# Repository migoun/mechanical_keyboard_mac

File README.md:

# Mechanical Keyboard on Mac with simple backlight<br>
This is an example for building a custom mechanical keyboard from scratch. I use it on a Mac, but there is no hardwired difference to a PC keyboard. I even kept the keymapping, because Mac OS can switch the Command and Option keys natively.<br>
Besides the technical side, I'll also write about my experience with manufacturers and stores, where I got all the parts. I also made a few beginner mistakes, which other beginners can avoid by reading this. This whole story is written for beginners.
<br><br>

I've built 2 keyboards with the same layouts but different components. <br><br>
1.) Cherry MX Brown Switches, Custom printed keycaps, green LEDs, black / transparent acrylic case<br>
<br>
<br>
<br>
2.) Gateron black switches, chrome- and bronze sprayed keycaps, fully transparent acrylic case and amber LEDs<br>
<br>
<br>
<br>

<div id="toc_container">
<p class="toc_title">Contents</p>
<ul class="toc_list">
    <li><a href="#crashcourse">Crash Course</a></li>    
    <li><a href="#layoutcreation">Layout Creation</a></li>
    <li><a href="#schematic">Schematic</a></li>
    <li><a href="#pcbdesign">PCB Design</a></li>
    <li><a href="#pcbproduction">PCB Production</a></li>
    <li><a href="#components">Components</a></li>
    <li><a href="#switches">Switches and Stabilizers</a></li>
    <li><a href="#keycaps">Keycaps</a></li>
    <li><a href="#lasering">Lasering a Sandwich Case</a></li>
    <li><a href="#soldering">Soldering and assembling</a></li>
    <li><a href="#firmware">Firmware</a></li>
    <li><a href="#mistakes">Mistakes</a></li>
</ul>
</div>

<h3 id="crashcourse">Crash Course</h3>
There's a phenomenal guide on how to build a keyboard here: https://github.com/ruiqimao/keyboard-pcb-guide <br>
If you don't have a clue yet, and have to start from the very beginning, then that's your starting point. I did it as well, because I had no idea from anything when I started. Through this guide I learned what components are needed to build a mechanical keyboard, what techniques / software is used to design electronic circuit boards, and a lot about electronics in general. Without this guide, I'd have never started.<br><br>

<h3 id="layoutcreation">Layout Creation</h3>
First, get an idea of how your keyboard should look like: http://www.keyboard-layout-editor.com<br>
This is mine: <a href="http://www.keyboard-layout-editor.com/#/gists/c6ae22aae21851b44d510154a7a343f7">Migouner</a>
<br>

<br>
<h3 id="schematic">Schematic</h3>
I did mostly everything like in the keyboard-pcb-guide tutorial. But I needed a different microcontroller, because I wanted to build a bigger keyboard with 85 keys. So with all rows and columns, I needed a total of 27 input pins for the matrix. Because QMK's firmware is used to flash the MCU, I took the one supported by QMK - AT90USB1286. It has a total of 48 input pins, so more than enough for Matrix and LED control pin.<br><br>
This is an overview of the board. Separated in 3 parts. LED circuit, keyboard matrix and the MCU section.<br><br>
<br><br>

MCU and Matrix circuit:<br>
<br>
<br>
<br>
For the matrix, I just looked at kbfirmware.com, the QMK firmware generator. I connected the keys in the schematic above exactly like the firmware tool defined my cols and rows:<br>
<br><br>

Aditionally the LED's for the backlighting:<br>
<br>
<br>

<h3 id="pcbdesign">PCB design</h3>
Normally you'd have to draw the PCB all by yourself, for all keys you have! I however, used a python script from here: https://github.com/ahtn/keyboard_case_and_pcb_gen<br>
You need the json output from KLE for this script to work. With this it generates a finished layout for all keys on the board. Then you have to put in everything else, MCU, diodes, resistors etc...<br><br>

But there are a few steps to get it working (on a mac). You need Homebrew and a lot of libraries, only then you can execute the script without getting an error:<br>
> brew install pip3 python3<br>
> pip3 install nose tornado solidpython numpy scipy kle pyparsing pyaml<br>
> git clone https://github.com/ahtn/keyboard_case_and_pcb_gen .<br>
<br>
Download json from KLE and then execute:<br>
> plate.py keyboard-layout.json<br>
<br><br>
By the time I needed to troubleshoot this script, I could have drawn the PCB already (now). But when I started, I didn't have any experience with KiCAD, and had no idea of positioning the keys, defining footprints etc...so I thought it would be easier to run a script.<br><br>

I'd also recommend, looking at the keyboard_example.py script in the python folder here. Because after importing your netlist into PCBnew, all existing pieces are on top of each other. So you have to click and drag each one to it's physical place on the board. Especially for the diodes, that can be frustrating, because you have to do this for every switch. That's what I wrote the python script for.<br><br>
After all, this is my result:<br>
<br><br>
You can use the silkscreen to print your own logo or text on the board. Kicad layers: F. Silk = Front Side, B. Silk = Back Side<br>
<br><br>

<h3 id="pcbproduction">PCB Production</h3>
After comparing a few manufacturers, I let it made at easyeda.com. You get an online quote immediately after uploading your Gerber files, and it was a very good price. But I ran into a massive delay because the german customs office. More in the mistakes section below. But the quality was perfectly fine. As I'm writing this, I already made 3 orders there, all of them were really well done and also cheap, compaired to other manufacturers.<br><br>

<h3>LED's for backlight</h3>
This is not as easy as it might sound like. An LED has about 2,1 - 2,3 Volts. Powering a single one with an Output pin of an Atmel Microchip is not a problem. Powering multiple LEDs needs a transistor for taking over the extra power. I took a MOSFET for that. (Before I started this project, I had no idea what a MOSFET is, or how an LED Circuit is powered. If you want to learn this, https://www.tinkercad.com/circuits is a great source for getting in touch with electronics (virtually).<br><br>

That turned out helpful, but I wanted to be 100% sure about this. The last thing I wanted, was that my keyboard burned to dust. So I got a cheap Arduino Uno (16&euro; with a lot of extras), also 2 extra MOSFETs from Amazon, and built up this scenario: <br>
<br>
There were only 330 Ohm resistors in the package, resulting in 5.5 mA going through each LED. I wanted about 8 or 9 mA for appropriate brightness (USB 2.0 can handle up to 500 mA in total). so I calculated here what I needed: http://tinyurl.com/y8kq7h9s<br>
<br>
Source: http://www.falstad.com/circuit/ (Also a great electronics simulator)<br>
<br>
200 Ohm resistors seemed fine for me. To wrap this up: The MOSFET is there because it takes power directly from the source and can handle a big amount of current. The gate controls the amount of current going through the transistor, controling the brightness of the LEDs. Therefore gate is connected to a PWM (Pulse Width Modulation) pin on the MCU. The special thing about this particular transistor is, it doesn't need current at the gate - only Voltage. This protects the Atmel chip and it's PWM pin. This circuit is in parallel mode, so these single color LED's cannot be controlled separately. It should be as easy as possible to build.<br>

<br>
<h3 id="components">Components</h3>
I've ordered everything at Digikey.com. But I recommend would read the shipping faq's carefully. I explain why in the mistakes secion below. Another good choice is mouser.com, it's the same great choice and filtering mechanism.<br>
One shitty thing though, shipping is very expensive (in both stores). So either you pay 20$ for shipping, or order something for more that 60$, in which case shipping is free. At least to Germany. So here's my component list:<br><br>
<table>
<tr><td><b>Quantity</b></td><td><b>Description</b></td></tr>
<tr><td>1</td>		<td>MCU AT90USB1286</td></tr>
<tr><td>10</td>		<td>RES 200 OHM 1% 1/4W 0805</td></tr>
<tr><td>1</td>		<td>CRYSTAL 16.0000MHZ 18PF SMD</td></tr>
<tr><td>1</td>		<td>CAP CER 1UF 16V X7R 0805</td></tr>
<tr><td>100</td>	<td>DIODE GEN PURP 100V 150MA SOD123</td></tr>
<tr><td>10</td>		<td>RES 22 OHM 5% 1/8W 0805</td></tr>
<tr><td>1</td>		<td>CAP CER 4.7UF 25V X5R 0805</td></tr>
<tr><td>1</td>		<td>SWITCH TACTILE SPST-NO 0.05A 12V</td></tr>
<tr><td>1</td>		<td>CONN RCPT MINI USB2.0 5POS SLD</td></tr>
<tr><td>2</td>		<td>CAP CER 22PF 50V C0G/NP0 0805</td></tr>
<tr><td>4</td>		<td>CAP CER 0.1UF 50V X7R 0805</td></tr>
<tr><td>10</td>		<td>RES 10K OHM 5% 1/8W 0805</td></tr>
<tr><td>2</td>		<td>RES SMD 1K OHM 0.1% 1/8W 0805</td></tr>
<tr><td>10</td>		<td>LED GREEN DIFFUSED 1206 SMD</td></tr>
<tr><td>1</td>		<td>MOSFET N-CH 30V 58A DPAK</td></tr>
</table>

<br>
<h3 id="switches">Switches and Stabilizers</h3>
I made the black board with Cherry brown switches, and the transparent one with Gateron black switches. You'll find a lot about switch types yourself, so I won't go into detail here. Interesting was that Gateron costs only half the price of Cherry. It claims to be the same, though. So I wanted to try out both of them. Same goes for stabilizers. Cherry stabs are more expensive than Costar. I used Cherry stabs for the Cherry switches and Costar for the Gateron switches. Good place to find stuff like that is at <a href="https://www.switchtop.com/">Switchtop</a>.<br>
<br>My result: The Cherry Brown Switches were easy to install and fit stable in the mounting holes "MX Openable Cutout". Also typing feels quite good on them. This combination of switches and plate is a robust and solid one. My personal favourite.<br>
The Gaterons are quite good, not a big difference to Cherry. However, the mounting holes I have chosen for the Gaterons when making the mounting plate - "MX + Alps Cutout" - it is known as the least stable. Now I know why. And it saved maybe 1 - 2$ maximum, when lasering the plate. So NOT recommendable. The other MX cutout could be used as well here.<br>
The Costar stabilizers are much more difficult to install, almost not stable at all, and I had to cut them with my wirecutter, so they didn't grind the bracket while going up and down. For me it wasn't fun using them. Clear advantage for the Cherry stabilizers, which fit pretty well and could be installed more quickly.<br>
Also a tube of Superlube is recommendable, greasing the stabilizers makes them go more smoothly.<br><br>
Important: PCB mounting is different from plate mounting. It changes your whole build. Stabilizers and switches are different, the PCB needs another design for drill holes etc, and the mounting plate's switch holes can be different. So be sure which mounting style you want. I went with plate mount, because more stability - the typing pressure is taken by the metal plate instead of the PCB, also fewer drilling holes on the PCB. If your PCB was made for PCB mount, it can also be used for plate mount. Not the other way.<br>

<br>
<h3 id="keycaps">Keycaps</h3>
For the black Rebound Games keyboard, I made custom keycaps at <a href="http://www.maxkeyboard.com/">MaxKeyboard</a>. They got templates for vector software, I use Inkscape. There are some limitations with the colors, but that was fine for my design. So I uploaded my Inkscape file and ordered the key set. Prices for custom printed key sets start at only 20$, so I could live with the color limitations.<br>
What wasn't so nice, some keys were slightly damaged. Looked like burn marks on the edges, but still fully functional. At least the printing was good.
<br><br>
For the second one I've ordered the cheapest keyset I could find on ebay, about 10&euro;. I sprayed them in bronze and chrome colors. In combination with the fully transparent case and the amber LEDs, it should get a futuristic style.<br>

<br>

<br>
<h3 id="lasering">Lasering a sandwich case</h3>
A very handy tool and also your starting point for case design: <a href="http://builder.swillkb.com/">builder.swillkb.com</a><br>
It creates all parts of a sandwich case keyboard, you just have to put in your layout from keyboard-layout-editor.com, and adjust the settings, it's well documented.<br>
<ul>
    <li>Mounting plate<br>
    For most plate mounted MX switches, the plate must be exactly 1.5mm thick. I let it made at <a href="https://www.laserboost.com/">Laserboost</a> in Barcelona and chose natural carbon steel as material. It was the cheapest metal, and I wanted to spray it another color anyway. So I didn't care about finishing. I was super satisfied with the end result!<br>  <br> One plate hat holes for Cherry switches only, the other one for Gateron switches and Costar stabilizers.
    </li><br>
    <li>Acrylic case<br>
    For top-, bottom- and open layers, I found reasonable prices at local companies in Germany. Because I found all the online services for lasercutting acrylic plates way to expensive. The two open layers are 5mm thick each, transparent acryl. Very solid, as it should be. Top- and bottom layers are 1mm each, black acryl. The second keyboard got transparent VIVAK material for top and bottom. It's like acryl but cheaper, I wanted to give it a try. The 1mm plates look fine, but are pretty wobbly. I thought they would be as hard as the thicker plates, but never mind. They don't have to carry something, so it doesn't matter.<br>
    
    </li><br>
    <li>Screws<br>
    My edge padding on the case is 7.4mm. That's the distance from the keys to the border of the case. In the middle of the padding, there are holes for screws. I made 6 in total. Diameter is 3.5mm, needed for M3 screws. It fits perfectly. On the bottom I used nut covers to fixate the screw. It also serves as a nice bottom foot for the keyboard. Finally I glued some rubber feet on the bottom, to get the right typing angle.
    </li><br>
</ul>

<br>
<h3 id="soldering">Soldering and assembling</h3>
If you never soldered SMDs (Surface Mount Devices), I highly recommend a practise pcb before start soldering your board. I bought one for 2&euro; on ebay. Also check out youtube tutorials on how to use Flux, or solder SMD, Microchips etc... You definitely need some magnifier as well, at least for controlling after soldering. I also have a magnifying headset for soldering. Because the chips's pins or the 0805 components are just pretty damn small.<br>
Best is to start with all components EXCEPT for the diodes and switches. A basic setup to make your computer recognize the chip when plugged in. This way you can react to issues at an early stage. And there can be issues! See mistakes section.<br>
If you built the board correctly, you will see a new USB device after plugging it into an USB port on your computer. It's named after the chip in the device manager (Windows), or on Mac "About this Mac" -> "More info".<br>
If you see your device there, you're good to go. If not, grab your multimeter for troubleshooting.<br>
<br>
Especially the diodes only work if the polarity is right. They cannot be the wrong way round. Everything else (besides the MCU and LEDs) can be either way. Capacitors, resistors and even the crystal.<br>
<br>
Once done soldering all components, the stabs and switches can be put in. First the stabs! Then some switches at the corners for fixating the plate on the PCB. If it fits nicely, all the other switches can be assembled and soldered as well. 
<br><br>
<br>
I sprayed the metal plate with a matt black color, it looked amazing afterwards! After the board is soldered and assembled to the mounting plate, all switches and stabs are in, the case can be screwed together and the keycaps put on.<br>

<br>
<h3 id="firmware">Firmware</h3>
I chose <a href="https://docs.qmk.fm">QMK firmware</a>, which is a great open source firmware for mechanical keyboards with lots of interesting features. Including backlight, key macros, debug mode etc...<br>
Your keyboard can be configured easily within the browser <a href="http://kbfirmware.com">kbfirmware.com</a>, things like keymap, pin mapping for the matrix, macros, basically everything. You don't have to write code at this point.<br>
After configuring, you can either download the hex file and flash it to the chip directly, or download the source code via zip file, and build the hex file yourself. That's what I did, because this way I could also customize the USB device Vendor and Version (in config.h), which you see in your device manager. Everything from building to flashing is well documented in the QMK docs. But there is something to take note of, below in the mistakes secion.<br>

<br>
<h3 id="mistakes">Mistakes</h3>
Ok here are some beginners mistakes, some were annoying, some stupid and some not hard to fix. I hope it help avoiding such things.
<ul>
    <li>Ordering with DHL<br>
    DHL scammed me so hard. I chose DHL for shipping, not UPS. So it arrived at the customs office in Leipzig, I got an email saying: Do you want us to ship the package? If you're a reseller, it would cost you extra fees. I said no, I order as a private person, and also paid the order as one. They looked at my 100 diodes position and asked me, why would you order 100 pieces of something? You must be reselling those...So I had to explain them why I would need 100 diodes! At some point they believed me and were willing to ship it. I asked the person on the phone if it would cost me something, taxes, fees etc...? If so, I do NOT want the package to be delivered. They said no, it does NOT cost anything, and shipped it. 4 weeks later I got a letter from DHL in cooperation with customs, forcing me to pay 40 Euros!!! for DHL "services"! What services please? It was free shipping you bunch of criminals! So i bought at Digikey for 50&euro; (FREE SHIPPING), and DHL rips 40&euro; off my face. And you can't do shit about it. If you deny the payment, you get extra fees on top of it.<br>
    Next time I ordered with UPS on a Friday, on Monday I had it. And NO extra fees! So never trust DHL, don't believe a single word they say. And if you order there from another continent, record every phone call and get yourself very good lawyers!<br><br>  
    </li><br>
    <li>PCB<br>
    On my first attempt, I didn't get the computer recognize the device. It just nothing happend after plugging into different USB ports. But power on all the SMD components seemed fine after measuring with my multimeter. In the end, it was wrong PCB design! I didn't connect the VBus pin of the Microcontroller! That was incredible stupid because this pin is responsible for registering an USB device on the computer. Not only that, but on this pin there must be a capacitor, which I also didn't consider. So this was my try to fix it:<br><br>I bridged a capacitor to the pin. Of course it didn't work and i threw away all 5 PCB's!<br><br>At least I could keep the components and reuse them on the next board.<br><br>
    </li>
    <li>Hint<br>
    If you want to save money, it maybe a good idea to start small. This way you won't fail at the end product like I did. I had to order this PCB twice, second time with the VBus corrected. For 2$ you can design a little board like this and try it out, get used to micro chips and how they work. For me it worked right after soldering. <br> <br>I then connected some LEDs and switches from my Arduino and flashed QMK firmware on the chip. To make a 4 key keyboard. It worked perfectly fine.<br><br> At this point I was sure what I'm doing, and ready to spend more money for the next keyboard PCB.<br>
    </li><br>
    <li>Switch Cutouts<br>
    I forgot to rotate vertical keys on the PCB, in the Case &amp; Plate builder the cutouts were rotated automatically. So the return key and the two vertical keys on the numblock were rotated by 90&deg; on the mounting plate, but not on the PCB. The Cherry and Gateron switches both fit the holes anyway, but without fixating. They are kept there by soldering only. Luckily assembling was possible anyway with Cherry. With Costar however, no luck. The keycap wouldn't fit on a 90&deg; rotated switch with opposite Costar stabs. So I had to remove the stabs completely there, resulting in a wobbly key.<br>
    </li><br>
    <li>LEDs<br>
    The LEDs I've ordered were too weak. They almost didn't illuminate at all. Turns out they were "Indication" LEDs. What I needed though, were Illumination LEDs. I didn't know which parameter in the datasheet actually stands for light intensity, and found that "mcd" is the one (Millicandela). The LEDs just had 8 mcd, which is close to nothing. Then I've ordered some other LEDs on ebay for 2&euro;. They had about 550 mcd and were nice and bright! They are on the picture at the top, the green ones.<br>
    Of course they had to be of the same current (20mA) and mounting type 1206.<br>
    </li><br>
    <li>Firmware<br>
    QMK is awesome. I just found 2 issues:<br>
    If you download the zip file directly from the firmware builders website, you cannot compile it. Because the codebase on the website is too old. A workaround is to download the git repository from qmk - it's documented in their docs - take your keyboard's directory from your zip file (not the other files), and put it into the QMK repo you've just cloned with git, also into the keyboards folder. Rename the folder to ["your keyboards name"]. Just like all other folders in there.<br>
    Then you can build the hex file with this command: make ["your keyboards name"]<br>
    Then it still won't work, saying some event function cannot be found. Just delete the whole funtion from your keymap.c file and it should run.<br>
    Also the loop for the backlight breathing was not correct, it flickered and then restarted every time, looked strange. It must be fixed in quantum/quantum.c.<br> 
    </li><br>
</ul><br>
<br>
That's all I have to say about it. It was not cheap but I learned very much about electronics, PCB's, microcontrollers... and got an ass kicking keyboard now, which I use every day and indeed became my favourite one! So I feel like it was worth it :-) I hope it helps you guys who also want to start building a keyboard. Have fun!

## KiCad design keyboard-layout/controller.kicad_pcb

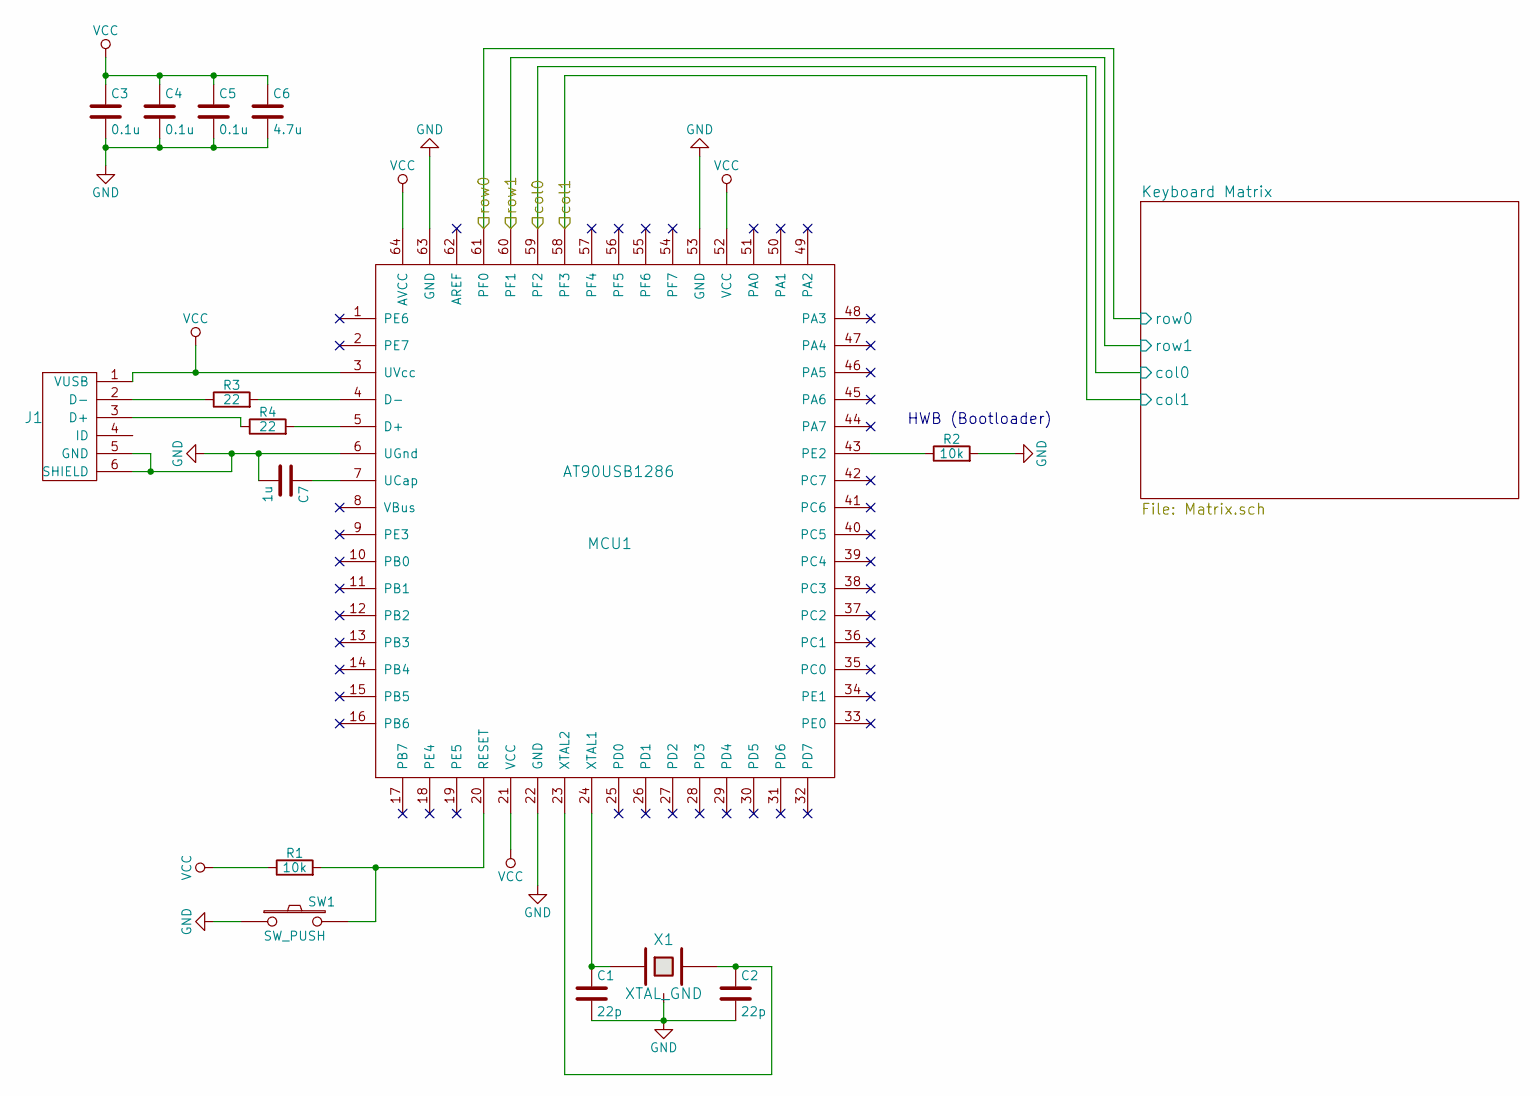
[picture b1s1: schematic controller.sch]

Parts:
C1, C2: 22p; C_0805_HandSoldering
C3, C4, C5: 0.1u; C_0805_HandSoldering
C6: 4.7u; C_0805_HandSoldering
C7: 1u; C_0805_HandSoldering
J1: USB_mini_micro_B; USB_miniB_hirose_5S8
MCU1: AT90USB1286; QFP80P1600X1600X120-64N
R1, R2: 10k; R_0805_HandSoldering
R3, R4: 22; R_0805_HandSoldering
SW1: SW_PUSH; SW_SPST_TL3342
X1: XTAL_GND; Crystal_SMD_SeikoEpson_FA238-4pin_3.2x2.5mm

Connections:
/Keyboard Matrix/col0: MCU1.59 (PF2); also elsewhere on the board
/Keyboard Matrix/col1: MCU1.58 (PF3); also elsewhere on the board
/Keyboard Matrix/row0: MCU1.61 (PF0); also elsewhere on the board
/Keyboard Matrix/row1: MCU1.60 (PF1); also elsewhere on the board
GND: C1.2, C2.2, C3.2, C4.2, C5.2, C6.2, C7.2, J1.5 (GND), J1.6 (SHIELD), MCU1.6 (UGnd), MCU1.22 (GND), MCU1.53 (GND), MCU1.63 (GND), R2.2, SW1.1, X1.3
unnamed: C1.1, MCU1.24 (XTAL1), X1.1
unnamed: C2.1, MCU1.23 (XTAL2), X1.2
unnamed: C7.1, MCU1.7 (UCap)
unnamed: J1.2 (D-), R3.1
unnamed: J1.3 (D+), R4.1
unnamed: MCU1.4 (D-), R3.2
unnamed: MCU1.5 (D+), R4.2
unnamed: MCU1.20 (RESET), R1.2, SW1.2
unnamed: MCU1.43 (PE2), R2.1
VCC: C3.1, C4.1, C5.1, C6.1, J1.1 (VUSB), MCU1.3 (UVcc), MCU1.21 (VCC), MCU1.52 (VCC), MCU1.64 (AVCC), R1.1

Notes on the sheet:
HWB (Bootloader)

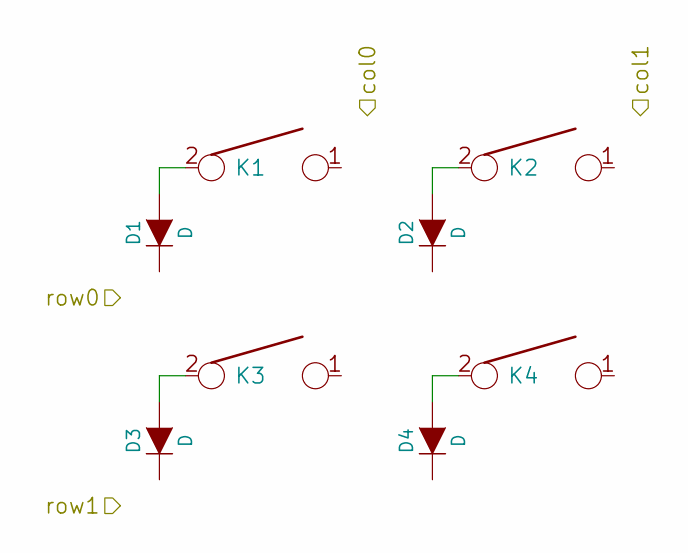
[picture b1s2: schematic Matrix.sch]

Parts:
D1, D2, D3, D4: D; D_SOD123_axial
K1, K2, K3, K4: KEYSW; MX1A

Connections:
/Keyboard Matrix/col0: K1.1, K3.1; also elsewhere on the board
/Keyboard Matrix/col1: K2.1, K4.1; also elsewhere on the board
/Keyboard Matrix/row0: D1.1 (K), D2.1 (K); also elsewhere on the board
/Keyboard Matrix/row1: D3.1 (K), D4.1 (K); also elsewhere on the board
unnamed: D1.2 (A), K1.2
unnamed: D2.2 (A), K2.2
unnamed: D3.2 (A), K3.2
unnamed: D4.2 (A), K4.2

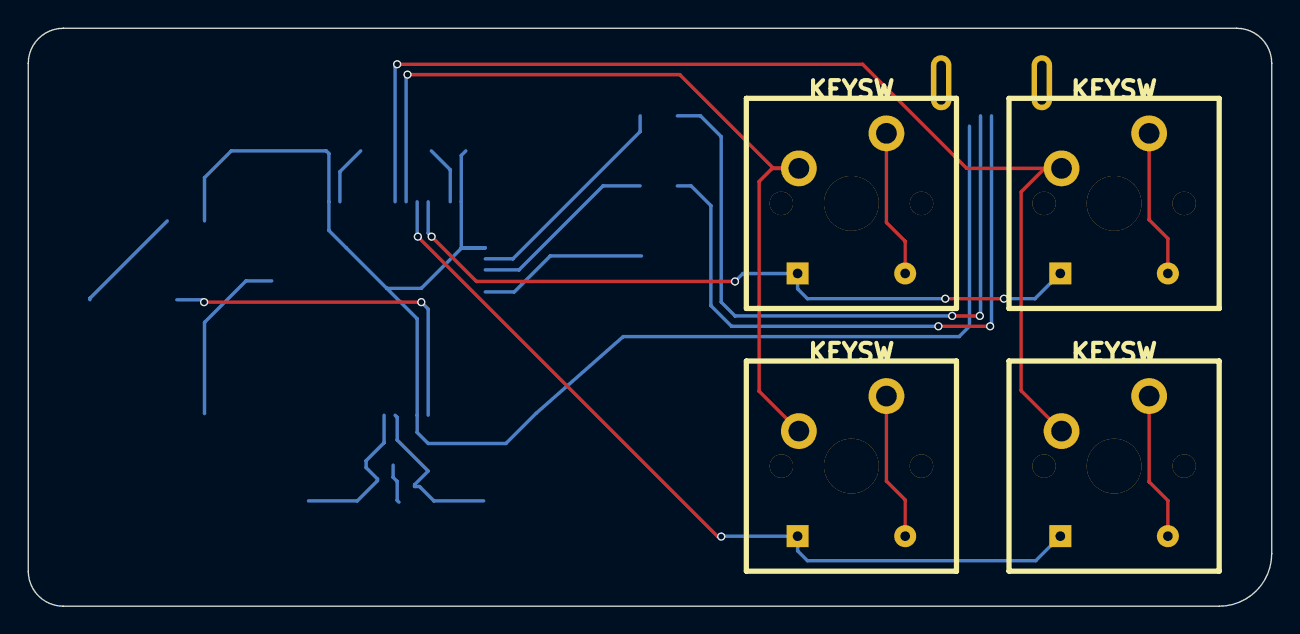
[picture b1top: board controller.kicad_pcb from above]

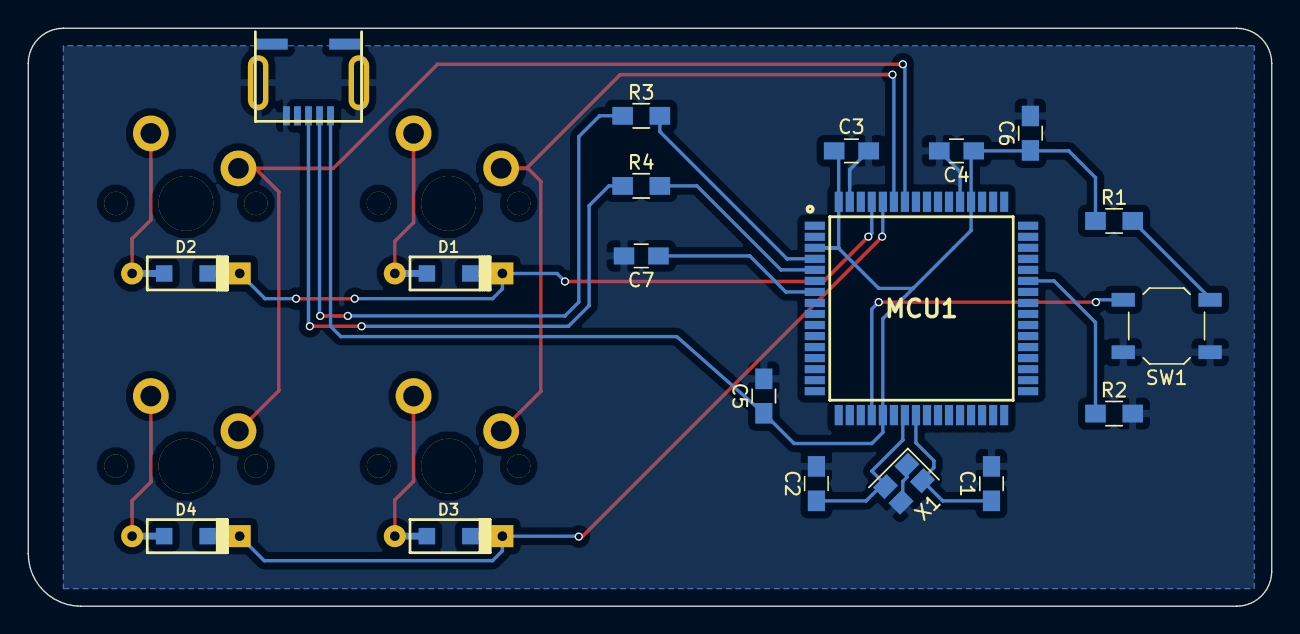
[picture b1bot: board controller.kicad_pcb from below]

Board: 2 copper layers, 90.2 x 41.9 mm, 23 parts (19 on the bottom side), 19 nets.

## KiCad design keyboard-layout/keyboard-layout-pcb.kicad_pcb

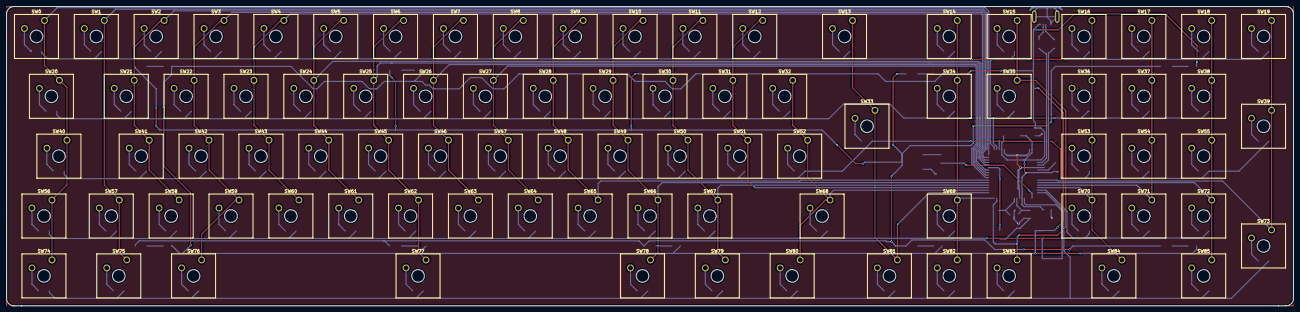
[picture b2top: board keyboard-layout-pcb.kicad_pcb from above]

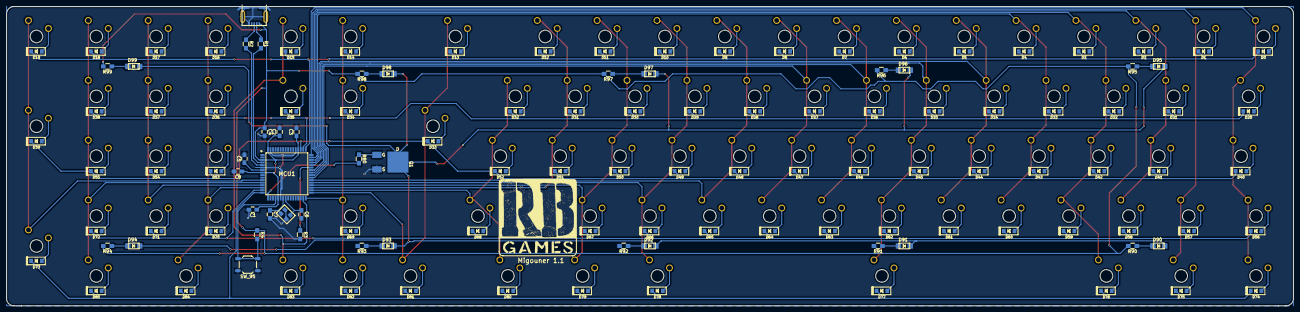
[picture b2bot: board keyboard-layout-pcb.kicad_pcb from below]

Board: 2 copper layers, 408.5 x 95.0 mm, 210 parts (124 on the bottom side), 136 nets.

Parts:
C1, C2, C3, C8: 0.1u; C_0805_HandSoldering
C4: 4.7u; C_0805_HandSoldering
C5: 1u; C_0805_HandSoldering
C6, C7: 22p; C_0805_HandSoldering
D0, D1, D2, D3, D4, D5, D6, D7, D8, D9, D10, D11, D12, D13, D14, D15, D16, D17, D18, D19, D20, D21, D22, D23, D24, D25, D26, D27, D28, D29, D30, D31, D32, D33, D34, D35, D36, D37, D38, D39, D40, D41, D42, D43, D44, D45, D46, D47, D48, D49, D50, D51, D52, D53, D54, D55, D56, D57, D58, D59, D60, D61, D62, D63, D64, D65, D66, D67, D68, D69, D70, D71, D72, D73, D74, D75, D76, D77, D78, D79, D80, D81, D82, D83, D84, D85: D; D_SOD123W_hand
D90, D91, D92, D93, D94, D95, D96, D97, D98, D99: LED; SMD_LED_Green_Migist
J1: USB_mini_micro_B; USB_miniB_hirose_5S8
MCU1: AT90USB1286; QFP80P1600X1600X120-64N
Q1: Mosfet; MOSFET
R1, R2: 22; R_0805_HandSoldering
R3, R4: 10k; R_0805_HandSoldering
R80: 1k; R_0805_HandSoldering
R90, R91, R92, R93, R94, R95, R96, R97, R98, R99: R; R_0805_HandSoldering
SW0, SW1, SW2, SW3, SW4, SW5, SW6, SW7, SW8, SW9, SW10, SW11, SW12, SW14, SW15, SW16, SW17, SW18, SW19, SW21, SW22, SW23, SW24, SW25, SW26, SW27, SW28, SW29, SW30, SW31, SW32, SW34, SW35, SW36, SW37, SW38, SW41, SW42, SW43, SW44, SW45, SW46, SW47, SW48, SW49, SW50, SW51, SW52, SW53, SW54, SW55, SW57, SW58, SW59, SW60, SW61, SW62, SW63, SW64, SW65, SW66, SW67, SW69, SW70, SW71, SW72, SW81, SW82, SW83, SW85: KEYSW; SW_Cherry_MX1A_1.00u_Plate
SW13, SW84: KEYSW; SW_Cherry_MX1A_2.00u_Plate
SW20: KEYSW; SW_Cherry_MX1A_1.50u_Plate
SW33: KEYSW; SW_Cherry_MX1A_ISOEnter_Plate
SW39, SW73: KEYSW; SW_Cherry_MX1A_2.00u_Vertical_Plate
SW40: KEYSW; SW_Cherry_MX1A_1.75u_Plate
SW56, SW74, SW75, SW76, SW78, SW79, SW80: KEYSW; SW_Cherry_MX1A_1.25u_Plate
SW68: KEYSW; SW_Cherry_MX1A_2.75u_Plate
SW77: KEYSW; SW_Cherry_MX1A_6.25u_Plate
SW_95: SW_PUSH; SW_SPST_TL3342
X1: XTAL_GND; FA-238

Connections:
/Keyboard Matrix/col0: MCU1.48, SW0.1, SW20.1, SW40.1, SW56.1, SW74.1
/Keyboard Matrix/col1: MCU1.47, SW1.1, SW57.1, SW75.1
/Keyboard Matrix/col2: MCU1.46, SW2.1, SW21.1, SW41.1, SW58.1
/Keyboard Matrix/col3: MCU1.45, SW3.1, SW22.1, SW42.1, SW59.1, SW76.1
/Keyboard Matrix/col4: MCU1.44, SW4.1, SW23.1, SW43.1, SW60.1
/Keyboard Matrix/col5: MCU1.42, SW5.1, SW24.1, SW44.1, SW61.1
/Keyboard Matrix/col6: MCU1.41, SW6.1, SW25.1, SW45.1, SW62.1, SW77.1
/Keyboard Matrix/col7: MCU1.40, SW7.1, SW26.1, SW46.1, SW63.1
/Keyboard Matrix/col8: MCU1.39, SW8.1, SW27.1, SW47.1, SW64.1
/Keyboard Matrix/col9: MCU1.38, SW9.1, SW28.1, SW48.1, SW65.1
/Keyboard Matrix/col10: MCU1.37, SW10.1, SW29.1, SW49.1, SW66.1, SW78.1
/Keyboard Matrix/col11: MCU1.36, SW11.1, SW30.1, SW50.1, SW67.1, SW79.1
/Keyboard Matrix/col12: MCU1.35, SW12.1, SW31.1, SW51.1
/Keyboard Matrix/col13: MCU1.34, SW32.1, SW52.1, SW68.1, SW80.1
/Keyboard Matrix/col14: MCU1.33, SW13.1, SW33.1, SW81.1
/Keyboard Matrix/col15: MCU1.32, SW14.1, SW34.1, SW69.1, SW82.1
/Keyboard Matrix/col16: MCU1.31, SW15.1, SW35.1, SW83.1
/Keyboard Matrix/col17: MCU1.14, SW16.1, SW36.1, SW53.1, SW70.1, SW84.1
/Keyboard Matrix/col18: MCU1.13, SW17.1, SW37.1, SW54.1, SW71.1
/Keyboard Matrix/col19: MCU1.12, SW18.1, SW38.1, SW55.1, SW72.1, SW85.1
/Keyboard Matrix/col20: MCU1.11, SW19.1, SW39.1, SW73.1
/Keyboard Matrix/row0: D0.1, D1.1, D2.1, D3.1, D4.1, D5.1, D6.1, D7.1, D8.1, D9.1, D10.1, D11.1, D12.1, D13.1, D14.1, D15.1, D16.1, D17.1, D18.1, D19.1, MCU1.49
/Keyboard Matrix/row1: D20.1, D21.1, D22.1, D23.1, D24.1, D25.1, D26.1, D27.1, D28.1, D29.1, D30.1, D31.1, D32.1, D34.1, D35.1, D36.1, D37.1, D38.1, MCU1.50
/Keyboard Matrix/row2: D33.1, D39.1, D40.1, D41.1, D42.1, D43.1, D44.1, D45.1, D46.1, D47.1, D48.1, D49.1, D50.1, D51.1, D52.1, D53.1, D54.1, D55.1, MCU1.51
/Keyboard Matrix/row3: D56.1, D57.1, D58.1, D59.1, D60.1, D61.1, D62.1, D63.1, D64.1, D65.1, D66.1, D67.1, D68.1, D69.1, D70.1, D71.1, D72.1, MCU1.15
/Keyboard Matrix/row4: D73.1, D74.1, D75.1, D76.1, D77.1, D78.1, D79.1, D80.1, D81.1, D82.1, D83.1, D84.1, D85.1, MCU1.16
/MCU/Mosfet: MCU1.17, R80.2
GND: C1.2, C2.2, C3.2, C4.2, C5.2, C6.2, C7.2, C8.2, J1.5, J1.6, MCU1.6, MCU1.22, MCU1.53, MCU1.63, Q1.3, R3.2, SW_95.1, X1.3
unnamed: C5.1, MCU1.7
unnamed: C6.1, MCU1.24, X1.1
unnamed: C7.1, MCU1.23, X1.2
unnamed: D0.2, SW0.2
unnamed: D1.2, SW1.2
unnamed: D2.2, SW2.2
unnamed: D3.2, SW3.2
unnamed: D4.2, SW4.2
unnamed: D5.2, SW5.2
unnamed: D6.2, SW6.2
unnamed: D7.2, SW7.2
unnamed: D8.2, SW8.2
unnamed: D9.2, SW9.2
unnamed: D10.2, SW10.2
unnamed: D11.2, SW11.2
unnamed: D12.2, SW12.2
unnamed: D13.2, SW13.2
unnamed: D14.2, SW14.2
unnamed: D15.2, SW15.2
unnamed: D16.2, SW16.2
unnamed: D17.2, SW17.2
unnamed: D18.2, SW18.2
unnamed: D19.2, SW19.2
unnamed: D20.2, SW20.2
unnamed: D21.2, SW21.2
unnamed: D22.2, SW22.2
unnamed: D23.2, SW23.2
unnamed: D24.2, SW24.2
unnamed: D25.2, SW25.2
unnamed: D26.2, SW26.2
unnamed: D27.2, SW27.2
unnamed: D28.2, SW28.2
unnamed: D29.2, SW29.2
unnamed: D30.2, SW30.2
unnamed: D31.2, SW31.2
unnamed: D32.2, SW32.2
unnamed: D33.2, SW33.2
unnamed: D34.2, SW34.2
unnamed: D35.2, SW35.2
unnamed: D36.2, SW36.2
unnamed: D37.2, SW37.2
unnamed: D38.2, SW38.2
unnamed: D39.2, SW39.2
unnamed: D40.2, SW40.2
unnamed: D41.2, SW41.2
unnamed: D42.2, SW42.2
unnamed: D43.2, SW43.2
unnamed: D44.2, SW44.2
unnamed: D45.2, SW45.2
unnamed: D46.2, SW46.2
unnamed: D47.2, SW47.2
unnamed: D48.2, SW48.2
unnamed: D49.2, SW49.2
unnamed: D50.2, SW50.2
unnamed: D51.2, SW51.2
unnamed: D52.2, SW52.2
unnamed: D53.2, SW53.2
unnamed: D54.2, SW54.2
unnamed: D55.2, SW55.2
unnamed: D56.2, SW56.2
unnamed: D57.2, SW57.2
unnamed: D58.2, SW58.2
unnamed: D59.2, SW59.2
unnamed: D60.2, SW60.2
unnamed: D61.2, SW61.2
unnamed: D62.2, SW62.2
unnamed: D63.2, SW63.2
unnamed: D64.2, SW64.2
unnamed: D65.2, SW65.2
unnamed: D66.2, SW66.2
unnamed: D67.2, SW67.2
unnamed: D68.2, SW68.2
unnamed: D69.2, SW69.2
unnamed: D70.2, SW70.2
unnamed: D71.2, SW71.2
unnamed: D72.2, SW72.2
unnamed: D73.2, SW73.2
unnamed: D74.2, SW74.2
unnamed: D75.2, SW75.2
unnamed: D76.2, SW76.2
unnamed: D77.2, SW77.2
unnamed: D78.2, SW78.2
unnamed: D79.2, SW79.2
unnamed: D80.2, SW80.2
unnamed: D81.2, SW81.2
unnamed: D82.2, SW82.2
unnamed: D83.2, SW83.2
unnamed: D84.2, SW84.2
unnamed: D85.2, SW85.2
unnamed: D90.1, D91.1, D92.1, D93.1, D94.1, D95.1, D96.1, D97.1, D98.1, D99.1, Q1.2
unnamed: D90.2, R90.1
unnamed: D91.2, R91.1
unnamed: D92.2, R92.1
unnamed: D93.2, R93.1
unnamed: D94.2, R94.1
unnamed: D95.2, R95.1
unnamed: D96.2, R96.1
unnamed: D97.2, R97.1
unnamed: D98.2, R98.1
unnamed: D99.2, R99.1
unnamed: J1.2, R1.1
unnamed: J1.3, R2.1
unnamed: MCU1.4, R1.2
unnamed: MCU1.5, R2.2
unnamed: MCU1.20, R4.2, SW_95.2
unnamed: MCU1.43, R3.1
unnamed: Q1.1, R80.1
VCC: C1.1, C2.1, C3.1, C4.1, C8.1, J1.1, MCU1.3, MCU1.8, MCU1.21, MCU1.52, MCU1.64, R4.1, R90.2, R91.2, R92.2, R93.2, R94.2, R95.2, R96.2, R97.2, R98.2, R99.2

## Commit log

2018-05-13 Initial
2018-05-22 mx footprints
2018-05-23 Keyboard Matrix
2018-05-25 Matrix complete
2018-05-27 pcb progress
2018-06-05 python scripting
2018-06-05 Bitz
2018-06-05 Merge
2018-06-05 Fresh
2018-06-06 cutting edge
2018-06-10 pcb without leds finished
2018-06-18 Leds
2018-06-19 3d Model
2018-06-20 3d board complete
2018-06-28 Documentation
2018-08-15 Keyboard 2
2018-08-30 Optimizations
2018-09-03 Case CAD
2018-09-03 PCB Production
2018-09-03 Case Measured
2018-09-06 Lasercuts
2018-10-01 docu
2018-10-28 doc update
2019-03-24 End, Home Shortkeys
2023-01-09 version 1.2
